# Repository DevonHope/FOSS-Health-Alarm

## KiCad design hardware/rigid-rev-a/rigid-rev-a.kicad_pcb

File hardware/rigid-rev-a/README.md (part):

# WakeBand rigid rev A (KiCad project)

4-layer 0.8 mm rigid board that replaces the flex design (archived in
`../flex-rev-a`). Routed, DRC clean, fab package in `fab/`. Last edited with
KiCad 10.0.3 (earlier revisions used 10.0.5; the file format is the same).

| Item | Value |
| --- | --- |
| Board | 33 x 15 mm, 1 mm corner radius, 0.8 mm FR4, ENIG |
| Pod | printed case rev A in `../case-rev-a` (one M2 screw); see below for the height stack |
| DRC | 0 violations, 0 unconnected, schematic parity 0 (1 documented exclusion); off-centre via ends checked as errors |
| Traces | straight or 45-degree segments only, 45-degree bends, every end on its pad or via centre (audit 2026-11-06, below) |
| ERC | 0 errors, 0 warnings |
| Vias | 140: 129 x 0.45/0.3 mm, 11 x 0.3/0.2 mm |
| Files | `rigid-rev-a-layout.pdf` (layers), `rigid-rev-a.pdf` (schematic), `fab/` |

## Stackup

JLCPCB JLC04081H-7628, 0.8 mm (also in `fab/gerbers/rigid-rev-a-job.gbrjob`):

| Layer | Use |
| --- | --- |
| F.Cu (L1, 35 um) | all SMT parts, two UART bench pads (J601 5-6, top edge), signal fan-out, GND pour |
| prepreg 7628, 0.21 mm | |
| In1.Cu (L2, 15 um) | solid GND, no tracks; no copper in the antenna keep-out |
| core 0.26 mm | |
| In2.Cu (L3, 15 um) | power jumps (VSYS, VBAT, VIN, VDD_2V0, LRA_P, nRESET) and signal routing; GND fill in the spare area |
| prepreg 7628, 0.21 mm | |
| B.Cu (L4, 35 um) | faces the cell and LRA: the four dock landing pads (J601 1-4), hand-solder pads TP201/TP202/TP501/TP502, JP201, signal routing, GND pour; no parts |

Track length by layer: F.Cu 208 mm, In2.Cu 205 mm, B.Cu 147 mm, In1.Cu 0.

## Orientation, outline and pod height

The board mounts **parts-side out** (changed 2026-11-06): F.Cu, with every
part, faces the case top, the pod's outer face. B.Cu has no parts and faces
the cell and the LRA, which sit between the board and the wrist.

**Dock contacts (changed 2026-11-07): four landing pads on B.** J601 pads
1-4 are Ø1.6 mm ENIG pads on B.Cu in a column at x 131.5, beside the LRA:
SWDCLK (y 101.1), SWDIO (103.3), GND (111.7), VIN (113.9). Four Mill-Max
0906-2 spring pins on the contact carrier in the wrist cover press on them
(see `../case-rev-a` and `../contact-carrier-rev-a`); nothing is soldered to
them. J601 pads 5-6 (UART_RX x 123.75, UART_TX x 121.75, y 101.6) stay on F
as bench test pads; the dock no longer carries UART (it uses SWD + RTT).
Coordinates below are KiCad board coordinates, with the board from
(100, 100) to (133, 115). The strip along the top edge (x 119.8-133) has
no parts, so the case top's land sits right on the board there and takes
the push of the top pair of spring pins.

Pod height, from the outer face (case rev A):

| Layer | mm |
| --- | --- |
| case top | 1.2 |
| tallest F part (L201, 0603 caps, SOD-123F) plus 0.2 mm | 1.3 |
| board | 0.8 |
| gap (B.Cu has no parts) | 0.2 |
| cell, up to | 5.0 |
| foam | 0.5 |
| wrist cover floor | 1.0 |
| **Total** | **about 10** (9 with a 4 mm cell) |

## Envelopes (Dwgs.User)

| Envelope | Where | Notes |
| --- | --- | --- |
| ISP2454 antenna keep-out | x 100-105, full height | rule area inside the U1 footprint: no tracks, vias or pours on any layer |
| 60 mAh cell, 17 x 13.5 mm | x 107-124, y 100.75-114.25 | under B; starts 2 mm past the keep-out; PCM and lead end at x = 124 |
| Ø8 LRA (Ø8.5 envelope) | centre (128.75, 107.5), x 124.5-133 | under B, far end of the board; circle top at y 103.25, bottom at 111.75 |

## 3D models

Every part on the board has a 3D model, except the test pads, the dock
pads, NT201 and JP201, which need none. KiCad 10 has no model for two
footprints, so `wakeband.3dshapes/` holds parametric ones (build123d; rebuild
with `pip install build123d`, then from this folder
`python wakeband.3dshapes/make_models.py wakeband.3dshapes`):

| Model | Used by | Size and source |
| --- | --- | --- |
| `InsightSiP_ISP2454_LGA-62_8x8mm.step` | U1 (also set in `wakeband.pretty`) | 8 x 8 x 1.0 mm, substrate plus overmould, pin-1 dot; size from the footprint |
| `Texas_DPY0002A_0.6x1mm_P0.65mm.step` | D602-D605 | 1.0 x 0.6 x 0.375 mm X1SON-2, bottom terminals, pin-1 band; TI MPSS034C |
| `LiPo_3.7V_60mAh_401215_PCM.step` | cell (off board) | 17 x 13 x 4.0 mm pouch with folded PCM at +X, lead stubs |
| `Vybronics_VG0832012_LRA_D8x3.25mm.step` | LRA (off board) | Ø8.0 x 3.25 mm can, lead tab at +X |
| `LED_TOGIALED_1615_RGB_CommonAnode.step` | D702 | 1.6 x 1.5 x 0.6 mm body and lens, pin-1 (anode) mark |
| `Kinetic_UTDFN-8_1.5x1.5mm_P0.4mm_EP1.45x0.8mm.step` | U202 | 1.5 x 1.5 x 0.5 mm UTDFN-8, pin-1 dot, terminals |

The paths use `${KIPRJMOD}`. D602-D605 use the KiCad library footprint
`Package_SON:Texas_DPY0002A_0.6x1mm_P0.65mm`; "Update footprint from library"
puts back the library's model path, which has no file in KiCad 10.

`make_placed.py` places the cell and the LRA in the board's STEP frame,
under B.Cu with a 0.2 mm gap: the cell centred at (115.5, 107.5) with its
lead end at x = 124, and the LRA centred at (128.75, 107.5) with its lead tab
turned towards TP501. The leads run to TP201 (bottom right) and TP202 (top
right) and to TP501/TP502. A clash check against the board's STEP finds no
overlaps. The tallest F part is now 1.1 mm (SW201 was removed on
2026-11-07); the charge LED is 0.6 mm.

## Placement

- **U1 ISP2454** at the left end, antenna end in the keep-out strip.
- **U401 LIS2DW12** just right of the module's top corner. C401 and C402
  sit right of it, 1.0 mm of track from pins 9 and 10; their GND pads share
  one via, and U401's GND pads 5-8 share another.
- **U201 nPM1304** in the middle. The BUCK1 parts sit left of it (see
  "Buck loop" below).
- **Charger caps** stacked right of U201, each beside its pin: C206
  (VBUSOUT, pin 22), C201 (VIN, pin 21), C205 (VSYS, pin 20), C202 (VBAT,
  pin 19). Their GND pads are joined by an F.Cu spine with three vias to
  In1 between the pads. R202 (VSET1) and R201 (DNP) sit below the stack.
  C203 sits under PMIC pin 12, offset left so pins 13-15 can escape.
- **JP201** (I_BAT jumper) on B in the bottom-right corner, between the
  cell's lead end and TP201, outside the cell and LRA outlines, so it can
  be cut for current measurement with the cell fitted.
- **Dock landing pads** J601 on B at x 131.5 (see Orientation). Their
  protection parts stay along the bottom edge: R601-R604 and D602-D605 (TI
  DPY package) between the module and D601 (VIN TVS).
- **U501 DRV2605L** at the right end over the LRA envelope, with C501, C502.
- **Hand-solder pads** on B (the cell side), 0.5 mm to other copper and
  mask at pad + 0.1 mm, all outside the cell and LRA outlines: TP201 (BAT+)
  at (129.0, 113.5) and JP201 in the bottom-right corner below the LRA
  circle; along the top edge TP502 (LRA-) at (125.5, 101.5), TP501 (LRA+)
  at (127.0, 101.5) and TP202 (BAT-, 1.5 mm pad) at (129.05, 101.6), all
  left of the dock landing pads. TP202 joins the B GND pour; TP501 has a
  filled via in its pad. TH201 sits on F over the cell, through the board.
- **Charge LED** D702 (RGB, 1.6 x 1.5 mm) at (130.225, 113.2), in SW201's old
  place at the bottom edge below U501, with its driver U202 (KTD2026) at
  (126.55, 113.2) and C208 (1 uF, VIN) at (128.1, 112.17). See "Charge LED"
  below.
- **Test pads**: TP702 (I2C_SDA) and TP704 (VDD_2V0) at the top edge near
  TH201, TP703 (I2C_SCL) left of U501, TP706 (VBAT) beside R201, TP401
  (ACC_INT2), TP701 (nRESET), TP705 (VSYS), TP707 (GND) and TP203
  (SHPHLD; with SW201 gone, this pad is the only way to pull SHPHLD low).
  TP704 has a filled via in its pad (flat after POFV, still
  probeable).

## Buck loop (nPM1304 BUCK1, pins 1-4)

Laid out after Nordic's reference: input cap across PVDD/PVSS1 at the pins,
output cap between the inductor and PVSS1, PVSS1 tied to GND only at the net
tie next to pin 2.

| Path (pad centre to pad centre, along the copper) | Now | Before the review |
| --- | --- | --- |
| C204.2 (PVSS1) to pin 2 | 1.7 mm, no vias | 5.4 mm |
| C204.1 (VSYS) to pin 4 (PVDD) | 1.7 mm, no vias | 3.3 mm, 2 vias |
| C207.2 (PVSS1) to pin 2 | 4.2 mm, no vias | 7.3 mm, 2 vias |
| C207.1 to L201.2 | 2.3 mm (pad centres are 2.2 mm apart) | 2.9 mm |
| NT201.1 to pin 2 | 3.0 mm | 9.6 mm |
| L201.1 to pin 3 (SW1) | 2.9 mm | 1.1 mm |
| C205.1 (VSYS) to pin 20 | 1.5 mm | 13.0 mm |
| pin 4 to pin 20 (VSYS) | 12.4 mm, 2 vias | 23.9 mm, 4 vias |

"Now" was measured after the 2026-11-06 trace clean-up, when every track
end sits on its pad centre; the clean-up moved these paths by 0.2 mm or
less.

- C204 sits 0.7 mm from pins 2 and 4. SW1 (0.3 mm) leaves pin 3 between
  C204's pads, under its body, to L201. The edge-to-edge copper of SW1 is
  2.2 mm: longer than before, the price of putting C204 across pins 2 and 4.
- C207 sits above L201; PVSS1 runs 0.4 mm wide from C207.2 through NT201.1
  and C204.2 to pin 2.
- NT201 sits on that PVSS1 link, 1.7 mm from pin 2, with its own GND via to
  In1 0.7 mm from its GND pad.
- Pin 1 (VOUT1, sense) drops through a via to In2 and lands at the
  L201.2/C207.1 node.
- Pin 4 and C204.1 change layer through two VSYS vias to two 0.2 mm In2
  tracks under the PMIC exposed pad (one in each gap between the EP via
  rows), which end in a via in C205.1's pad next to pin 20. Pin 32 joins
  through its own via. VSYS to U501/C501 runs on F from pin 32 along the
  top of the PMIC area.

## Routing

- Power: 0.4 mm on the battery path (BATT_P 0.5 mm, VBAT), 0.3 mm on
  VIN/VSYS/SW1/LRA, 0.4 mm on PVSS1 between the caps, 0.25 mm at the PMIC
  pins, 0.2 mm VSYS under the EP, 0.25 mm on VDD_2V0 where it leaves the
  buck. VBAT changes layer with two vias at each end. Single vias remain on
  VSYS (pin 32 and the via in C205.1), VIN (the via in C201.1, at
  (123.1, 111.75) and at the dock, (122.65, 113.2)), VDD_2V0 and LRA_P at
  U501 (129.15, 106.4). Each via is good for about 1 A, well above these
  currents.
- Signals: 0.12 mm tracks, 0.10 mm clearance, VDD_2V0 and REG 0.2 mm,
  routed with a scripted grid router because Freerouting crashed on this
  board, then cleaned up (see "Trace audit" below). The router keeps vias
  out of pads. I2C runs U401 - U1 - U201 - U501
  with test pads TP702/TP703.
- Dock lines (rework 2026-11-06): the pads moved from B (bottom edge) to F
  (top edge), and each line now runs from its pad across the board to its
  TVS and 100 ohm resistor at the bottom edge, then on to the module:
  UART_TX 28.8 mm / 3 vias, UART_RX 27.0 / 3, SWDIO 41.9 / 4 (round the
  module end), SWDCLK 27.3 / 2, VIN 23.8 mm / 3 vias to C201.1. These were
  laid by a small 3-layer grid router (F, In2, B; In1 stays solid GND) and
  then checked by DRC and the trace audit; three spots were laid by hand.
- Rules (in `rigid-rev-a.kicad_dru` and the netclasses): 0.10 mm clearance
  on all netclasses, 0.2 mm hole clearance, 0.2 mm from vias to other copper
  on inner layers, 0.5 mm around the hand-solder pads. Zones use 0.2 mm
  clearance.
- ANT_LINK (module pads 20 and 22) is joined on F.Cu, 0.65 mm long, right at
  the keep-out edge over the solid In1 GND.
- No F.Cu tracks inside the module's or the PMIC's pad ring (nRESET and
  some signals pass under the module on In2/B, outside the keep-out).
  VDD_2V0 passes under U401 between its pads, and REG and I2C pass under
  the U501 body; all are under solder mask.

## GND, stitching and vias

- In1 is solid GND. F, B and the spare area of In2 are GND pours (0.2 mm
  clearance, islands removed).
- Each F-side GND pad has its own via to In1 where there is room, plus
  stitching vias around the board edge and at the module's top and bottom
  (outside the keep-out).
- Shared GND vias: U401 pads 5-8 share one; C401 and C402 share one; the
  four charger caps share three on their GND spine. TP202 (BAT-) on B
  joins the B GND pour; the GND landing pad has a via at its edge.
- Each data TVS (D602-D605) has its own GND via about 0.8 mm from its GND
  pad.
- Two 0.3/0.2 mm GND vias under the U501 body tie the pin 4 and pin 8 pour
  pockets to In1.

| Vias | Count |
| --- | --- |
| 0.45/0.3, signal and power | 76 |
| 0.45/0.3, GND (incl. 9 in the nPM1304 exposed pad, 4 in module corner pads, 1 in dock pad 2) | 49 |
| 0.3/0.2, GND (8 in module pads, 2 under U501) | 10 |
| 0.3/0.2, nRESET (module pad 13) | 1 |
| Total | 136 |

### Vias in pads and POFV

The ISP2454 pads that sit inside the outer ring cannot be reached by a
track on F.Cu. Their outcome:

- **Interior GND pads** 8, 12, 14, 16, 18, 24 (column x = 105.2) and 21, 23
  (column x = 105.85) each have a 0.3/0.2 mm via in the pad. The large GND
  pads 1, 7, 25, 31 have 0.45/0.3 mm vias in the pad.
- **nRESET (pad 13)** has a 0.3/0.2 via in the pad and runs on In2 to TP701.
- **Pad 10** stays NC. The other inner pads are unused nets, left
  unconnected.

Other vias in pads: nine in the nPM1304 exposed pad, TP701 (nRESET), C201.1
(VIN), C205.1 (VSYS), TP704 (VDD_2V0), TP501 (LRA+), D601.1 (VIN), the
SWDCLK landing pad (J601.3, centre) and the edges of the VIN and GND landing
pads (J601.1, J601.2). All of these need JLCPCB's
**epoxy-filled and capped (POFV)** option, which fills every via on the
board.

## DRC and ERC

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
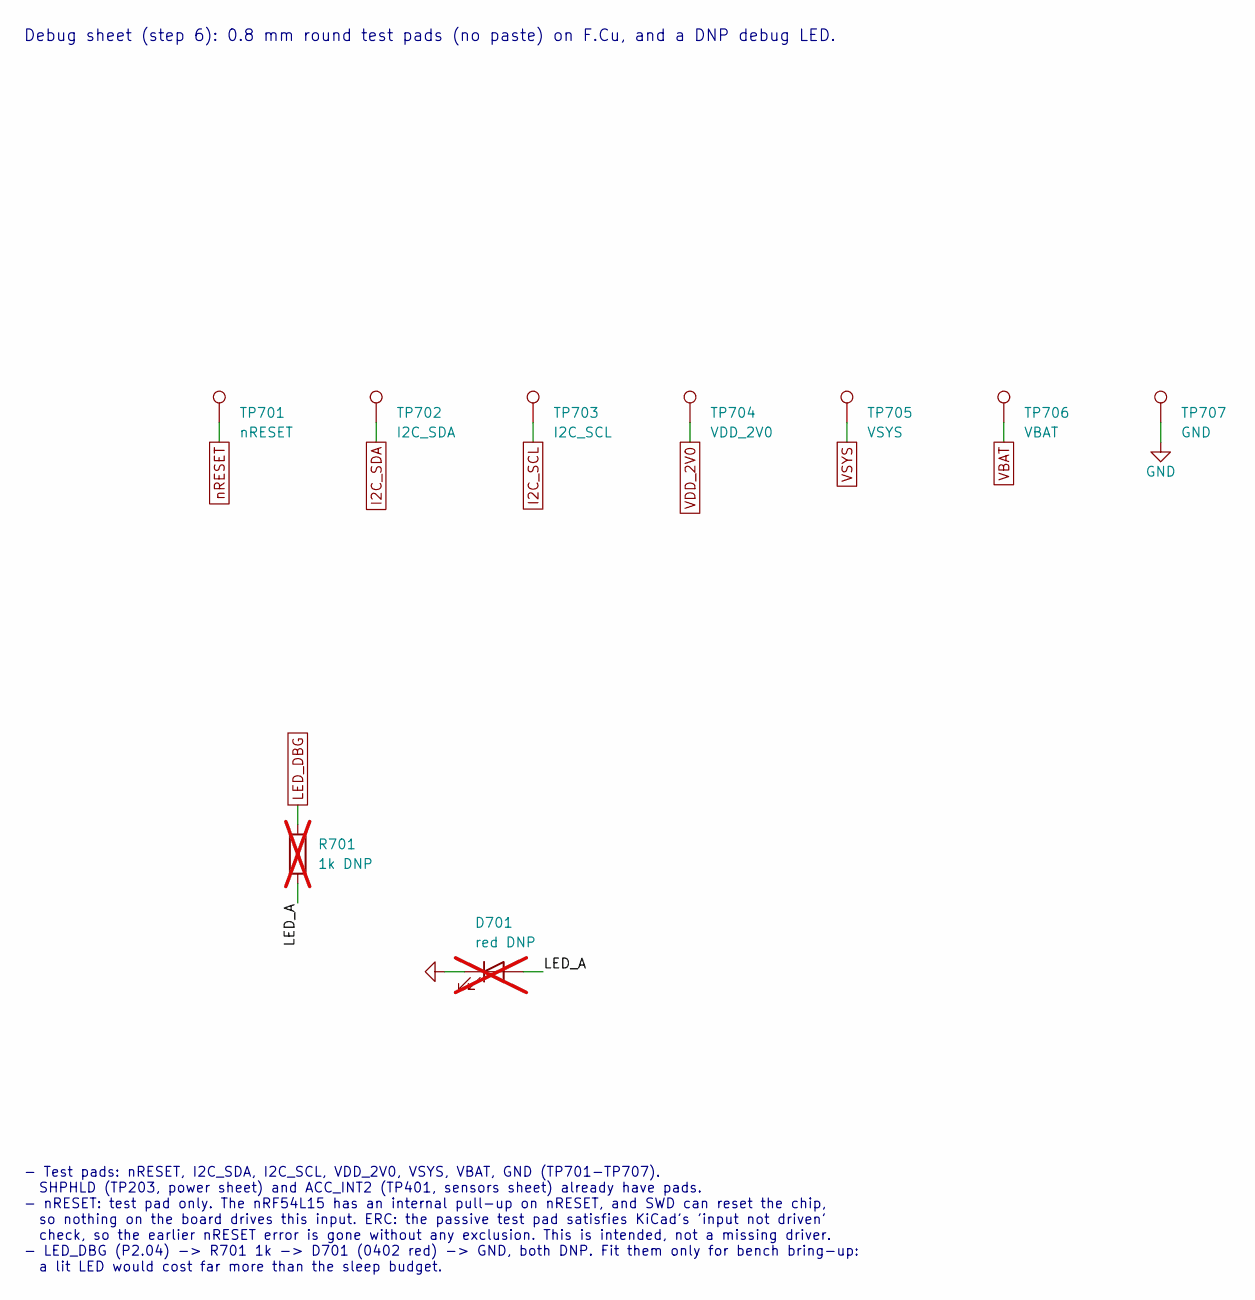
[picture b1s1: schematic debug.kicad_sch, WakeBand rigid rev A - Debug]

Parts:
D701: red DNP; LED_0402_1005Metric; MPN XINGLIGHT XL-1005SURC; LCSC C25503345; not fitted
R701: 1k DNP; R_0402_1005Metric; LCSC C11702; not fitted
TP701: nRESET; TestPoint_Pad_D0.8mm
TP702: I2C_SDA; TestPoint_Pad_D0.8mm
TP703: I2C_SCL; TestPoint_Pad_D0.8mm
TP704: VDD_2V0; TestPoint_Pad_D0.8mm
TP705: VSYS; TestPoint_Pad_D0.8mm
TP706: VBAT; TestPoint_Pad_D0.8mm
TP707: GND; TestPoint_Pad_D0.8mm

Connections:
/debug/LED_A: D701.2 (A), R701.2
GND: D701.1 (K), TP707.1; also elsewhere on the board
I2C_SCL: TP703.1; also elsewhere on the board
I2C_SDA: TP702.1; also elsewhere on the board
LED_DBG: R701.1; also elsewhere on the board
VBAT: TP706.1; also elsewhere on the board
VDD_2V0: TP704.1; also elsewhere on the board
VSYS: TP705.1; also elsewhere on the board
nRESET: TP701.1; also elsewhere on the board

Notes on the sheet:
- Test pads: nRESET, I2C_SDA, I2C_SCL, VDD_2V0, VSYS, VBAT, GND (TP701-TP707). SHPHLD (TP203, power sheet) and ACC_INT2 (TP401, sensors sheet) already have pads. - nRESET: test pad only. The nRF54L15 has an internal pull-up on nRESET, and SWD can reset the chip, so nothing on the board drives this 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
Debug sheet (step 6): 0.8 mm round test pads (no paste) on F.Cu, and a DNP debug LED.

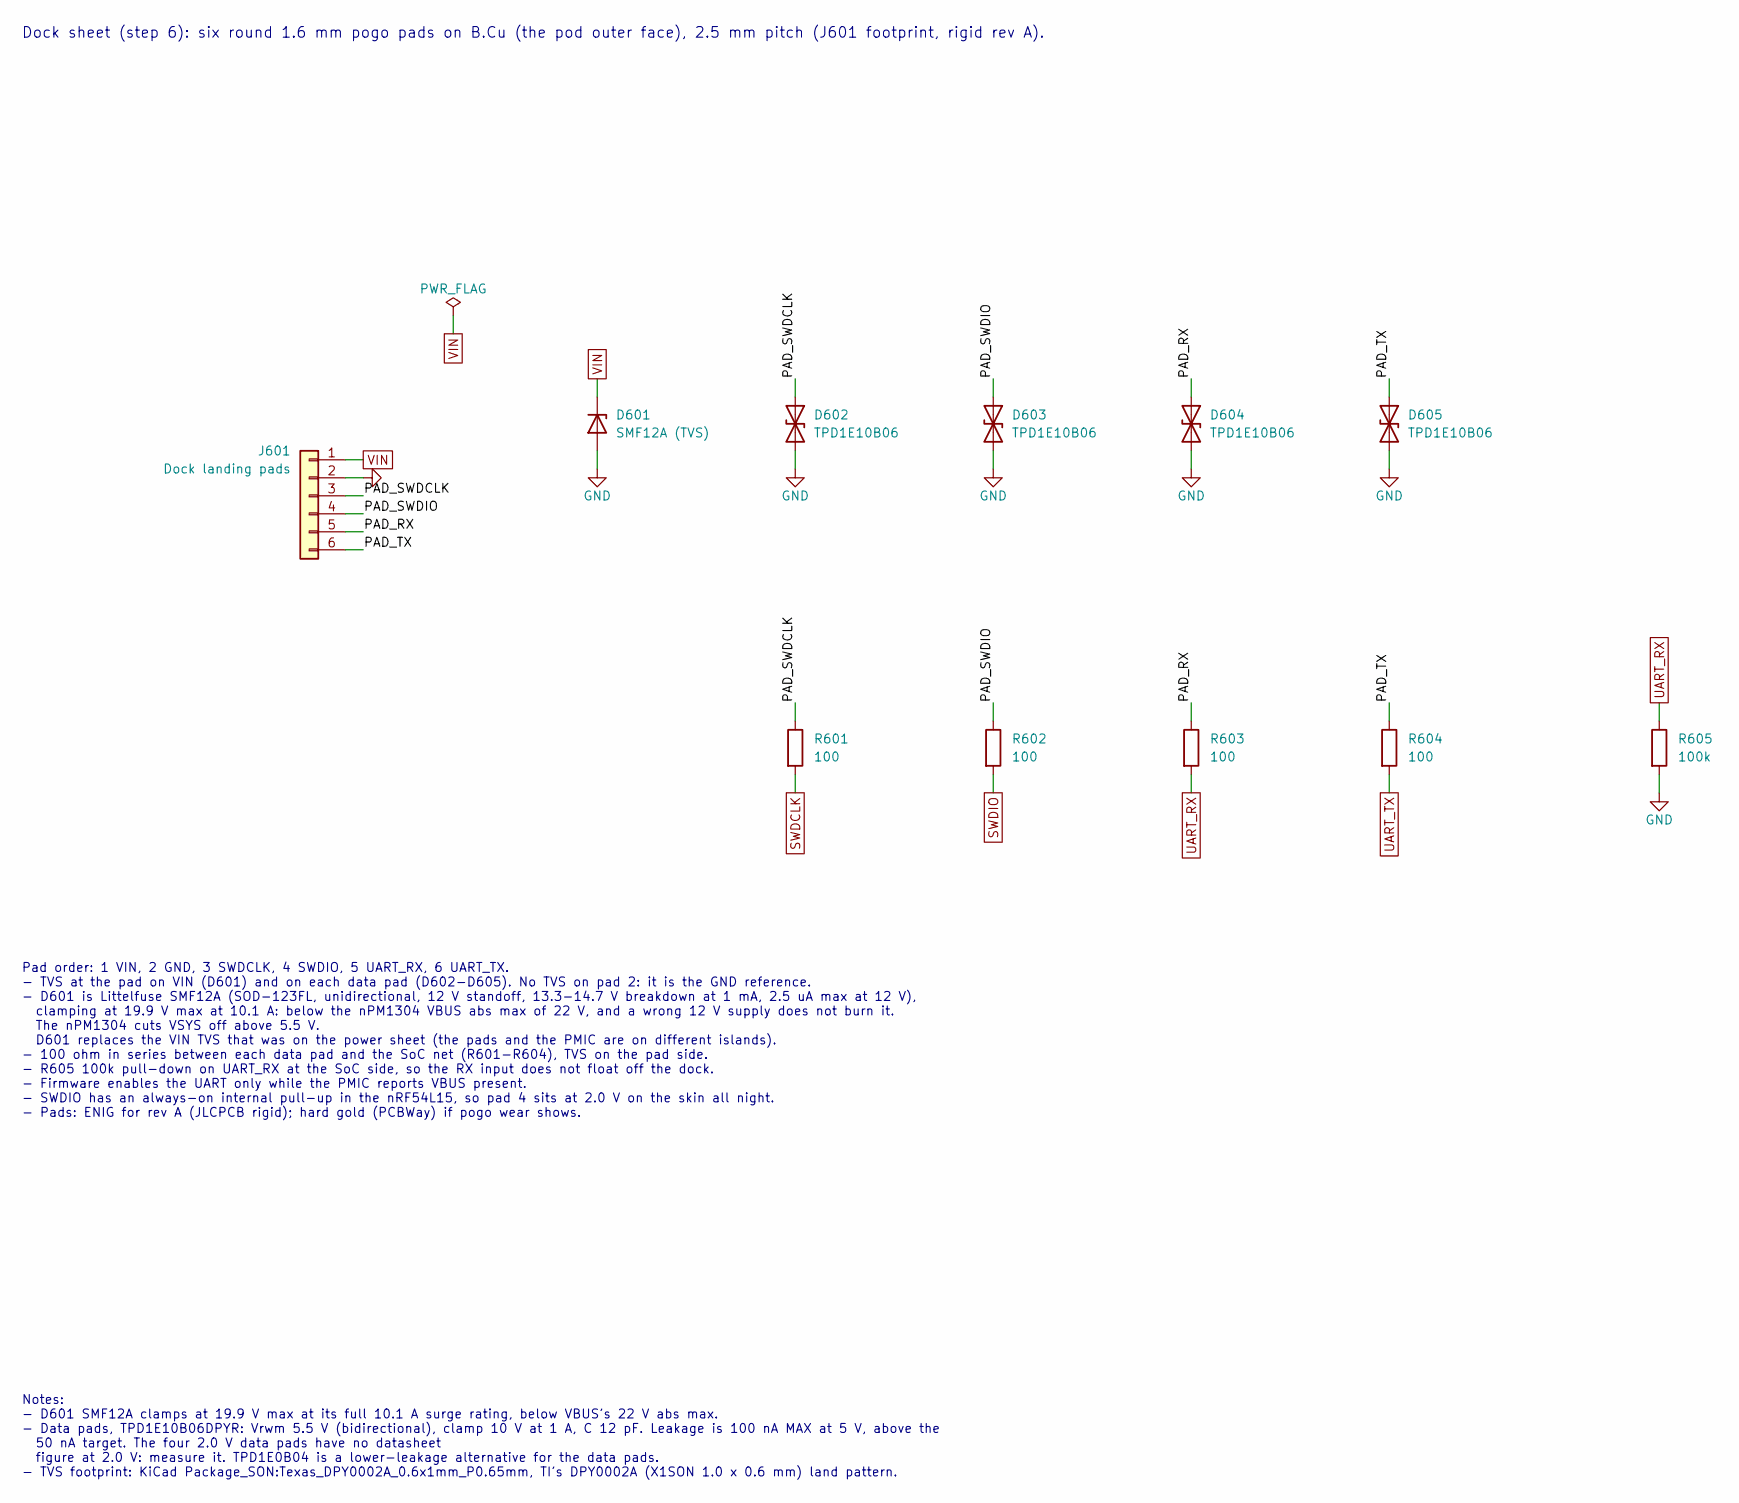
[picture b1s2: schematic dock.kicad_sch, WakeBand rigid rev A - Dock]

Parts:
D601: SMF12A (TVS); D_SOD-123F; MPN Littelfuse SMF12A; LCSC C207255
D602, D603, D604, D605: TPD1E10B06; Texas_DPY0002A_0.6x1mm_P0.65mm; MPN TI TPD1E10B06DPYR; LCSC C48260
J601: Dock landing pads; DockLanding_4xB_D1.6mm_2xUART
R601, R602, R603, R604: 100; R_0402_1005Metric; LCSC C25076
R605: 100k; R_0402_1005Metric; LCSC C25741

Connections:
/dock/PAD_RX: D604.1 (A1), J601.5, R603.1
/dock/PAD_SWDCLK: D602.1 (A1), J601.3, R601.1
/dock/PAD_SWDIO: D603.1 (A1), J601.4, R602.1
/dock/PAD_TX: D605.1 (A1), J601.6, R604.1
GND: D601.2 (A), D602.2 (A2), D603.2 (A2), D604.2 (A2), D605.2 (A2), J601.2, R605.2; also elsewhere on the board
SWDCLK: R601.2; also elsewhere on the board
SWDIO: R602.2; also elsewhere on the board
UART_RX: R603.2, R605.1; also elsewhere on the board
UART_TX: R604.2; also elsewhere on the board
VIN: D601.1 (K), J601.1; also elsewhere on the board

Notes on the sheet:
Pad order: 1 VIN, 2 GND, 3 SWDCLK, 4 SWDIO, 5 UART_RX, 6 UART_TX. - TVS at the pad on VIN (D601) and on each data pad (D602-D605). No TVS on pad 2: it is the GND reference. - D601 is Littelfuse SMF12A (SOD-123FL, unidirectional, 12 V standoff, 13.3-14.7 V breakdown at 1 mA, 2.5 uA max at 12 V), cla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
Dock sheet (step 6): six round 1.6 mm pogo pads on B.Cu (the pod outer face), 2.5 mm pitch (J601 footprint, rigid rev A).
Notes: - D601 SMF12A clamps at 19.9 V max at its full 10.1 A surge rating, below VBUS's 22 V abs max. - Data pads, TPD1E10B06DPYR: Vrwm 5.5 V (bidirectional), clamp 10 V at 1 A, C 12 pF. Leakage is 100 nA MAX at 5 V, above the 50 nA target. The four 2.0 V data pads have no datasheet figure at 2.0 V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

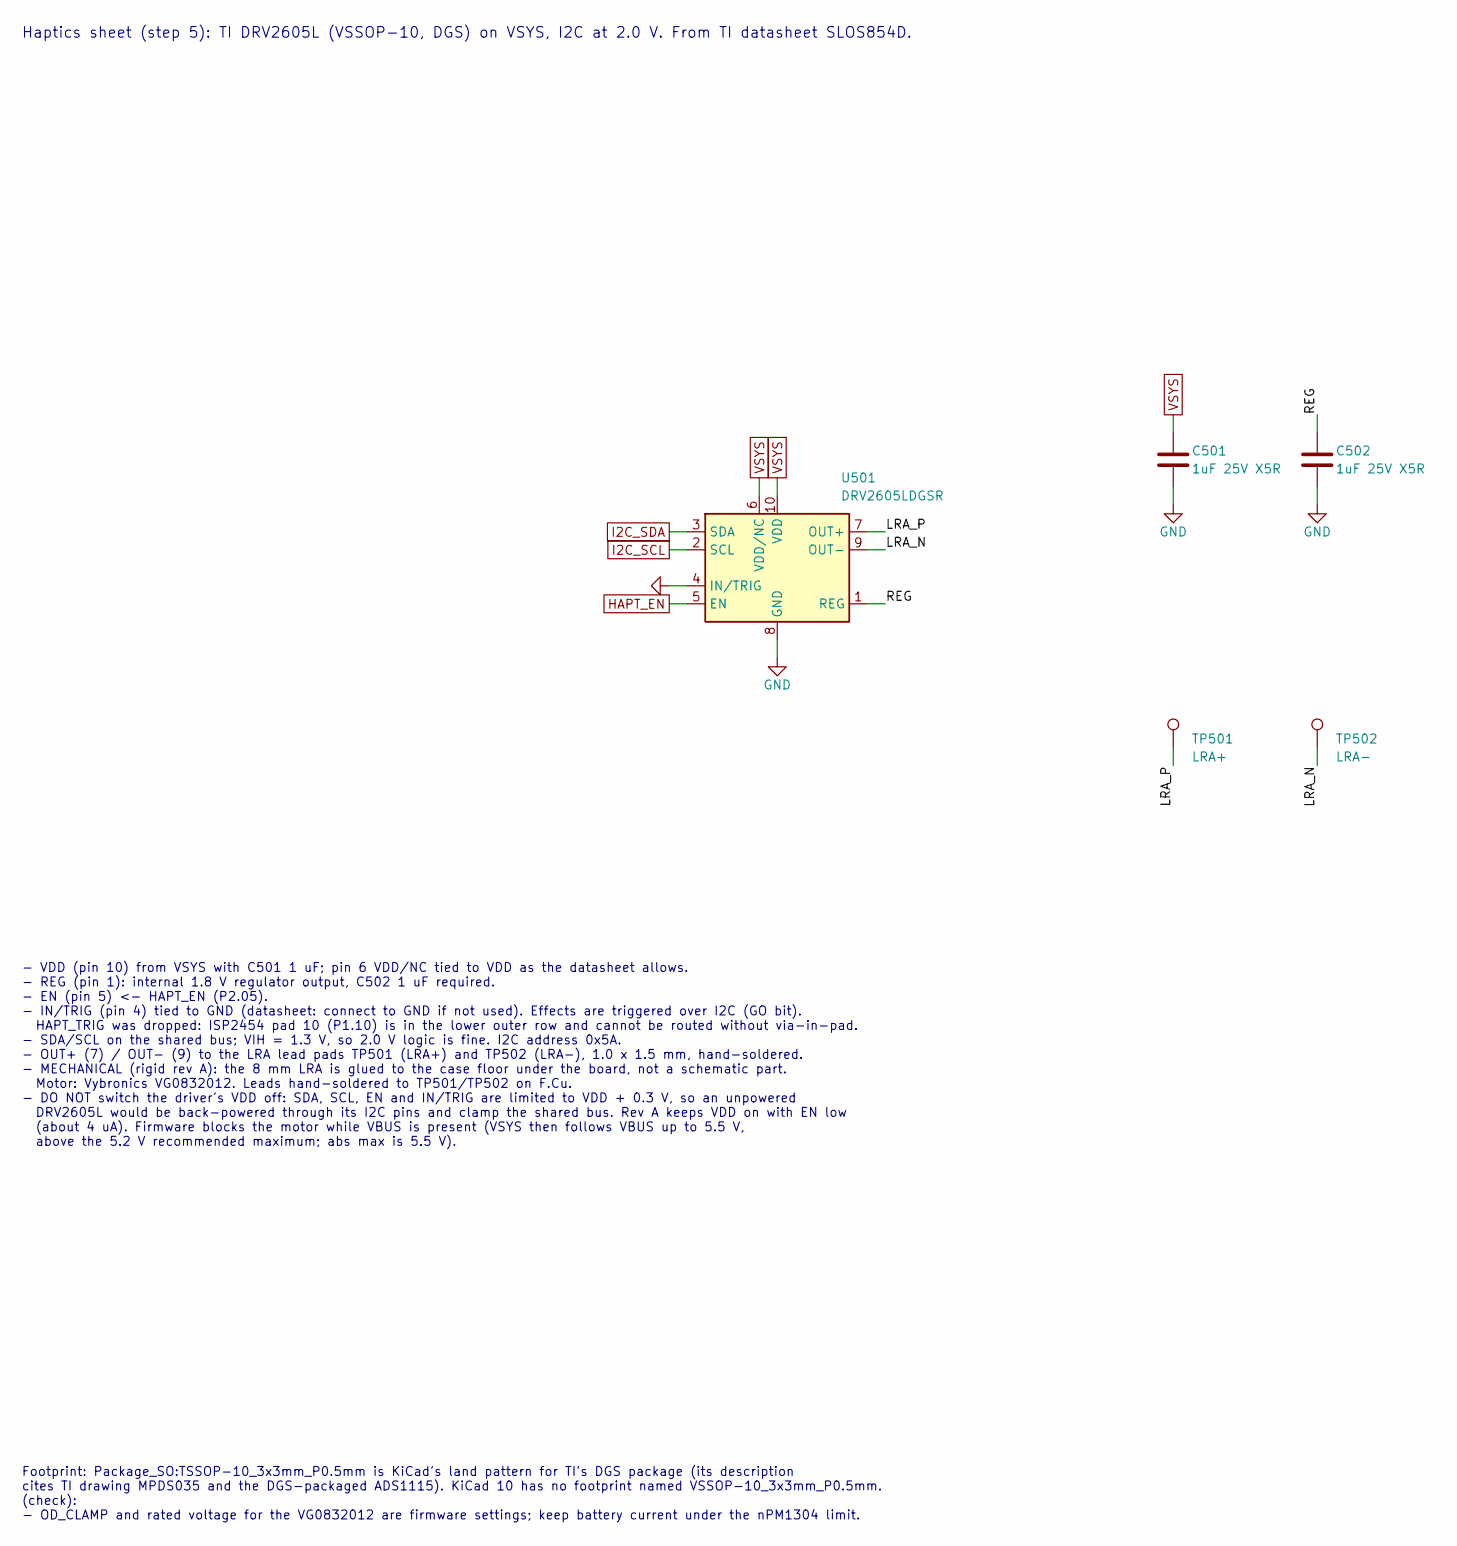
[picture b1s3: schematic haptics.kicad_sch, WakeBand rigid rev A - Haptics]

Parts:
C501, C502: 1uF 25V X5R; C_0402_1005Metric; LCSC C52923
TP501: LRA+; Pad_SMD_1.0x1.5mm
TP502: LRA-; Pad_SMD_1.0x1.5mm
U501: DRV2605LDGSR; TSSOP-10_3x3mm_P0.5mm; LCSC C527464

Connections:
/haptics/LRA_N: TP502.1, U501.9 (OUT-)
/haptics/LRA_P: TP501.1, U501.7 (OUT+)
/haptics/REG: C502.1, U501.1 (REG)
GND: C501.2, C502.2, U501.4 (IN/TRIG), U501.8 (GND); also elsewhere on the board
HAPT_EN: U501.5 (EN); also elsewhere on the board
I2C_SCL: U501.2 (SCL); also elsewhere on the board
I2C_SDA: U501.3 (SDA); also elsewhere on the board
VSYS: C501.1, U501.6 (VDD/NC), U501.10 (VDD); also elsewhere on the board

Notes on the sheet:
Footprint: Package_SO:TSSOP-10_3x3mm_P0.5mm is KiCad's land pattern for TI's DGS package (its description cites TI drawing MPDS035 and the DGS-packaged ADS1115). KiCad 10 has no footprint named VSSOP-10_3x3mm_P0.5mm. (check): - OD_CLAMP and rated voltage for the VG0832012 are firmware settings; kee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
Haptics sheet (step 5): TI DRV2605L (VSSOP-10, DGS) on VSYS, I2C at 2.0 V. From TI datasheet SLOS854D.
- VDD (pin 10) from VSYS with C501 1 uF; pin 6 VDD/NC tied to VDD as the datasheet allows. - REG (pin 1): internal 1.8 V regulator output, C502 1 uF required. - EN (pin 5) <- HAPT_EN (P2.05). - IN/TRIG (pin 4) tied to GND (datasheet: connect to GND if not used). Effects are triggered over I2C (GO b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

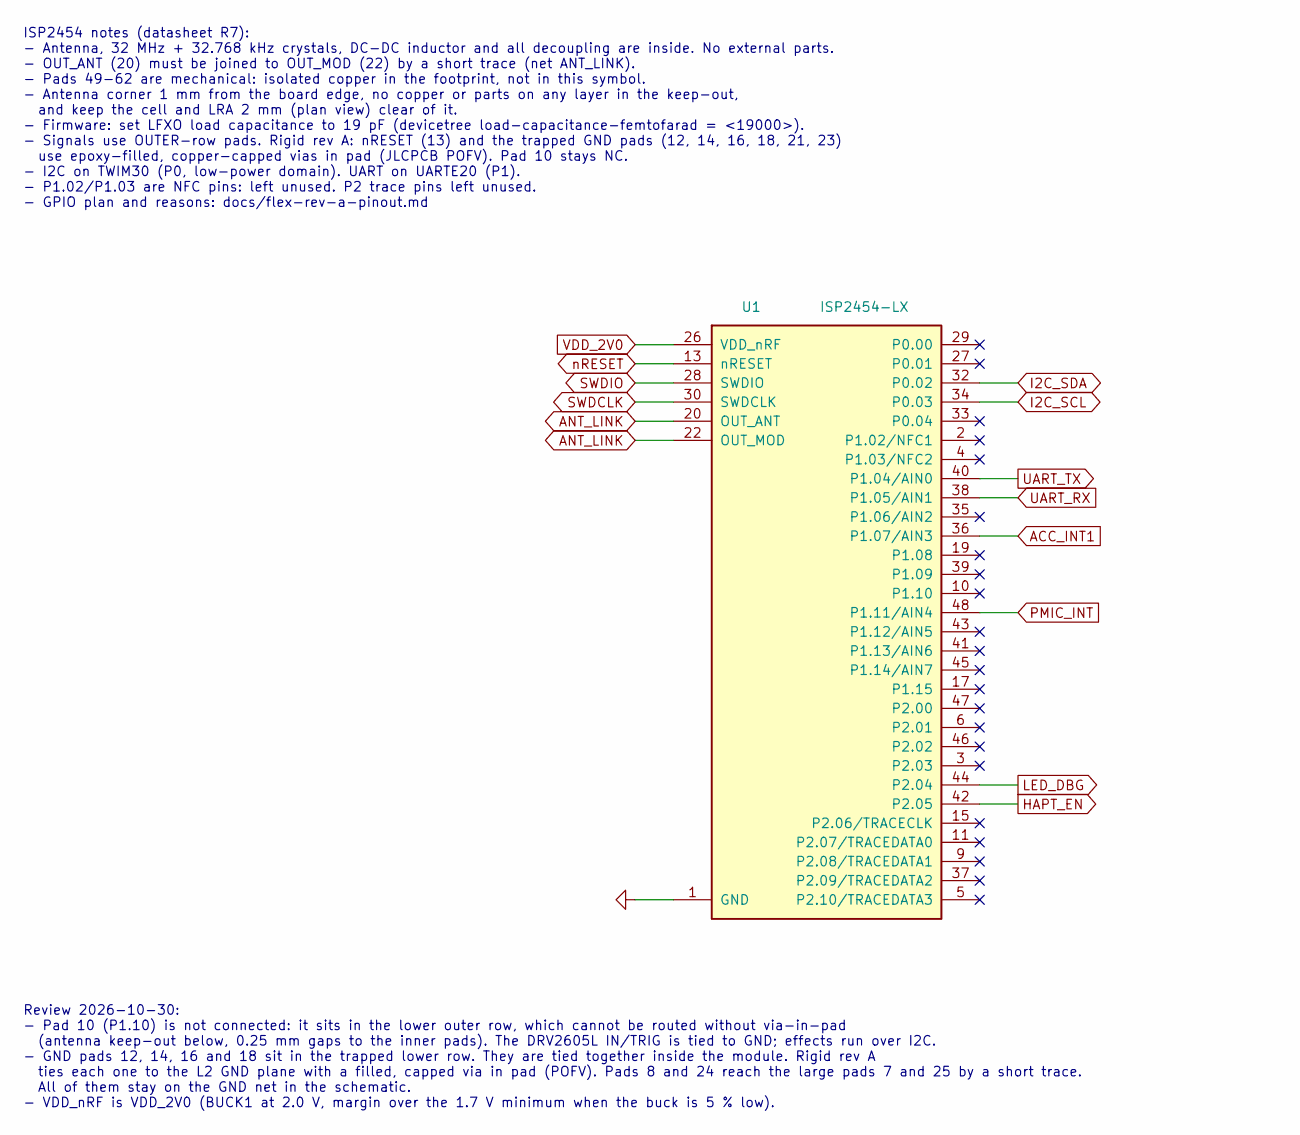
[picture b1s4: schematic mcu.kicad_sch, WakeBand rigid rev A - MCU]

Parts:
U1: ISP2454-LX; InsightSiP_ISP2454_LGA-62_8x8mm

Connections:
ACC_INT1: U1.36 (P1.07/AIN3); also elsewhere on the board
ANT_LINK: U1.20 (OUT_ANT), U1.22 (OUT_MOD)
GND: U1.1 (GND), U1.7 (GND), U1.8 (GND), U1.12 (GND), U1.14 (GND), U1.16 (GND), U1.18 (GND), U1.21 (GND), U1.23 (GND), U1.24 (GND), U1.25 (GND), U1.31 (GND); also elsewhere on the board
HAPT_EN: U1.42 (P2.05); also elsewhere on the board
I2C_SCL: U1.34 (P0.03); also elsewhere on the board
I2C_SDA: U1.32 (P0.02); also elsewhere on the board
LED_DBG: U1.44 (P2.04); also elsewhere on the board
PMIC_INT: U1.48 (P1.11/AIN4); also elsewhere on the board
SWDCLK: U1.30 (SWDCLK); also elsewhere on the board
SWDIO: U1.28 (SWDIO); also elsewhere on the board
UART_RX: U1.38 (P1.05/AIN1); also elsewhere on the board
UART_TX: U1.40 (P1.04/AIN0); also elsewhere on the board
VDD_2V0: U1.26 (VDD_nRF); also elsewhere on the board
nRESET: U1.13 (nRESET); also elsewhere on the board

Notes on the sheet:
Review 2026-10-30: - Pad 10 (P1.10) is not connected: it sits in the lower outer row, which cannot be routed without via-in-pad (antenna keep-out below, 0.25 mm gaps to the inner pads). The DRV2605L IN/TRIG is tied to GND; effects run over I2C. - GND pads 12, 14, 16 and 18 sit in the trapped lower 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
ISP2454 notes (datasheet R7): - Antenna, 32 MHz + 32.768 kHz crystals, DC-DC inductor and all decoupling are inside. No external parts. - OUT_ANT (20) must be joined to OUT_MOD (22) by a short trace (net ANT_LINK). - Pads 49-62 are mechanical: isolated copper in the footprint, not in this symbol. -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

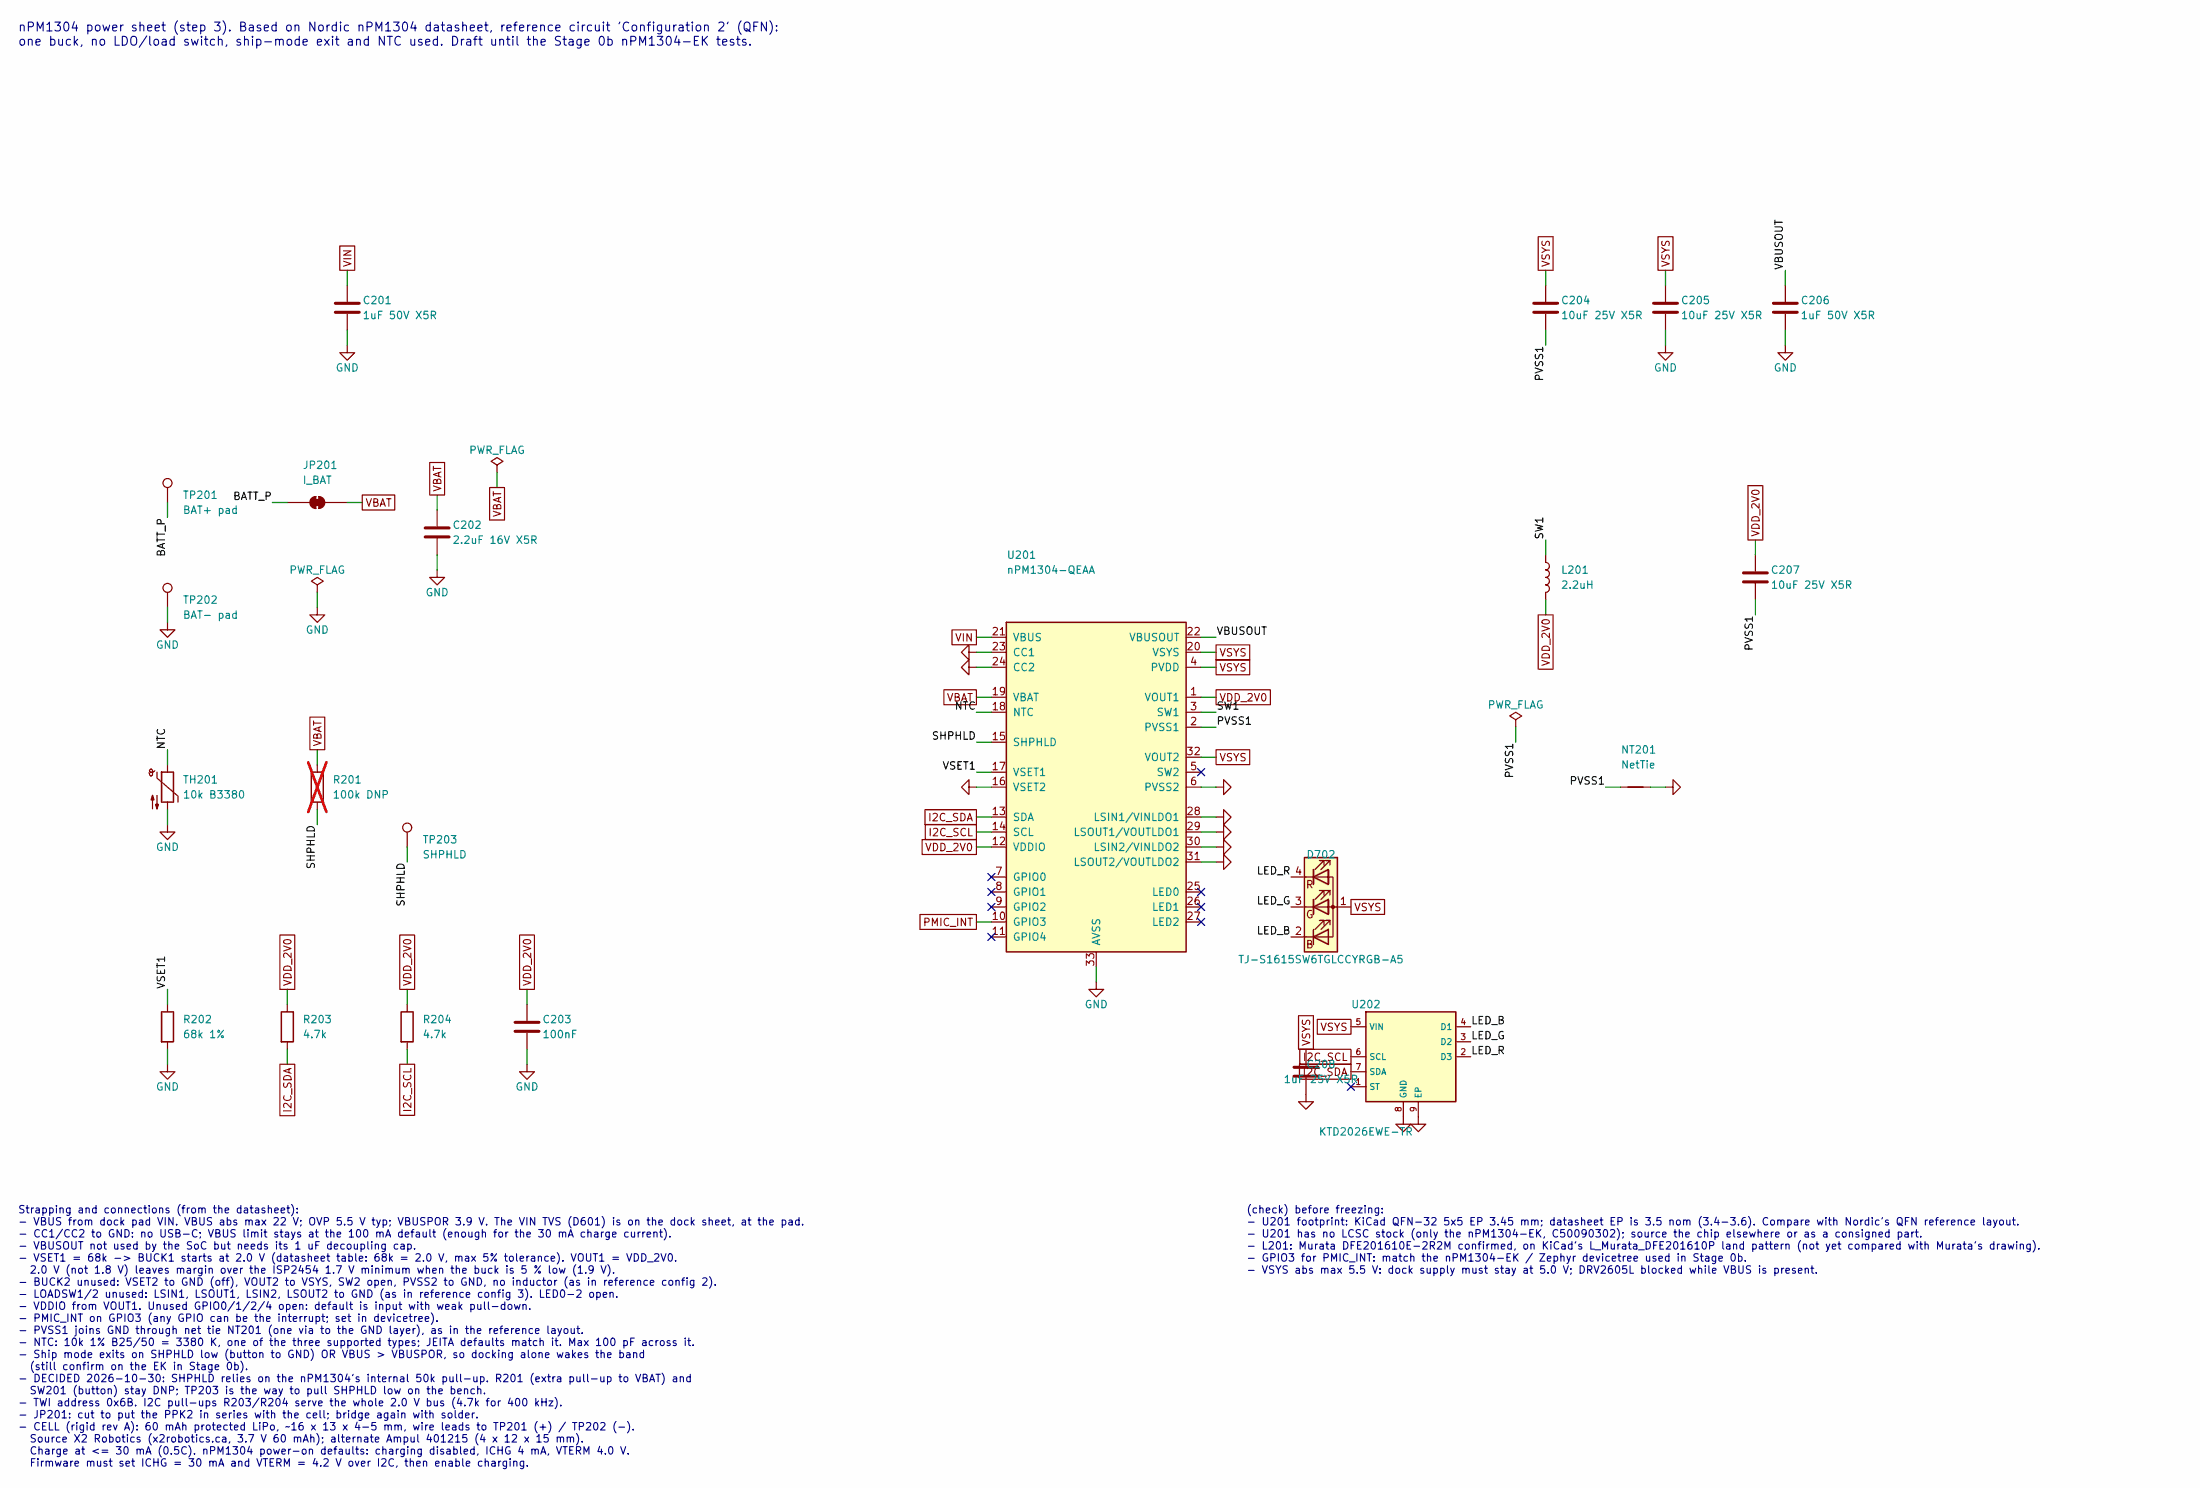
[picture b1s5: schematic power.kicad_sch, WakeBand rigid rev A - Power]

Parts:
C201, C206: 1uF 50V X5R; C_0603_1608Metric; LCSC C15849
C202: 2.2uF 16V X5R; C_0603_1608Metric; LCSC C23630
C203: 100nF; C_0402_1005Metric; LCSC C1525
C204, C205, C207: 10uF 25V X5R; C_0603_1608Metric; LCSC C96446
C208: 1uF 25V X5R; C_0402_1005Metric; LCSC C52923
D702: TJ-S1615SW6TGLCCYRGB-A5; LED_TOGIALED_1615_RGB_CommonAnode; LCSC C273610
JP201: I_BAT; SolderJumper-2_P1.3mm_Bridged_RoundedPad1.0x1.5mm
L201: 2.2uH; L_Murata_DFE201610P; MPN Murata DFE201610E-2R2M; LCSC C337891
NT201: NetTie; NetTie-2_SMD_Pad0.5mm
R201: 100k DNP; R_0402_1005Metric; LCSC C25741; not fitted
R202: 68k 1%; R_0402_1005Metric; LCSC C36871
R203, R204: 4.7k; R_0402_1005Metric; LCSC C25900
TH201: 10k B3380; R_0402_1005Metric; MPN Murata NCP15XH103F03RC; LCSC C77131
TP201: BAT+ pad; TestPoint_Pad_2.0x2.0mm
TP202: BAT- pad; TestPoint_Pad_1.5x1.5mm
TP203: SHPHLD; TestPoint_Pad_1.0x1.0mm
U201: nPM1304-QEAA; QFN-32-1EP_5x5mm_P0.5mm_EP3.45x3.45mm
U202: KTD2026EWE-TR; Kinetic_UTDFN-8_1.5x1.5mm_P0.4mm_EP1.45x0.8mm; MPN Kinetic KTD2026EWE-TR

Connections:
/power/BATT_P: JP201.1 (A), TP201.1
/power/LED_B: D702.2 (BK), U202.4 (D1)
/power/LED_G: D702.3 (GK), U202.3 (D2)
/power/LED_R: D702.4 (RK), U202.2 (D3)
/power/NTC: TH201.1, U201.18 (NTC)
/power/PVSS1: C204.2, C207.2, NT201.1, U201.2 (PVSS1)
/power/SHPHLD: R201.2, TP203.1, U201.15 (SHPHLD)
/power/SW1: L201.1, U201.3 (SW1)
/power/VBUSOUT: C206.1, U201.22 (VBUSOUT)
/power/VSET1: R202.1, U201.17 (VSET1)
GND: C201.2, C202.2, C203.2, C205.2, C206.2, C208.2, NT201.2, R202.2, TH201.2, TP202.1, U201.6 (PVSS2), U201.16 (VSET2), U201.23 (CC1), U201.24 (CC2), U201.28 (LSIN1/VINLDO1), U201.29 (LSOUT1/VOUTLDO1), U201.30 (LSIN2/VINLDO2), U201.31 (LSOUT2/VOUTLDO2), U201.33 (AVSS), U202.8 (GND), U202.9 (EP); also elsewhere on the board
I2C_SCL: R204.2, U201.14 (SCL), U202.6 (SCL); also elsewhere on the board
I2C_SDA: R203.2, U201.13 (SDA), U202.7 (SDA); also elsewhere on the board
PMIC_INT: U201.10 (GPIO3); also elsewhere on the board
VBAT: C202.1, JP201.2 (B), R201.1, U201.19 (VBAT); also elsewhere on the board
VDD_2V0: C203.1, C207.1, L201.2, R203.1, R204.1, U201.1 (VOUT1), U201.12 (VDDIO); also elsewhere on the board
VIN: C201.1, U201.21 (VBUS); also elsewhere on the board
VSYS: C204.1, C205.1, C208.1, D702.1 (A), U201.4 (PVDD), U201.20 (VSYS), U201.32 (VOUT2), U202.5 (VIN); also elsewhere on the board

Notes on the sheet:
Strapping and connections (from the datasheet): - VBUS from dock pad VIN. VBUS abs max 22 V; OVP 5.5 V typ; VBUSPOR 3.9 V. The VIN TVS (D601) is on the dock sheet, at the pad. - CC1/CC2 to GND: no USB-C; VBUS limit stays at the 100 mA default (enough for the 30 mA charge current). - VBUSOUT not use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
(check) before freezing: - U201 footprint: KiCad QFN-32 5x5 EP 3.45 mm; datasheet EP is 3.5 nom (3.4-3.6). Compare with Nordic's QFN reference layout. - U201 has no LCSC stock (only the nPM1304-EK, C50090302); source the chip elsewhere or as a consigned part. - L201: Murata DFE201610E-2R2M confirme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
nPM1304 power sheet (step 3). Based on Nordic nPM1304 datasheet, reference circuit 'Configuration 2' (QFN): one buck, no LDO/load switch, ship-mode exit and NTC used. Draft until the Stage 0b nPM1304-EK tests.

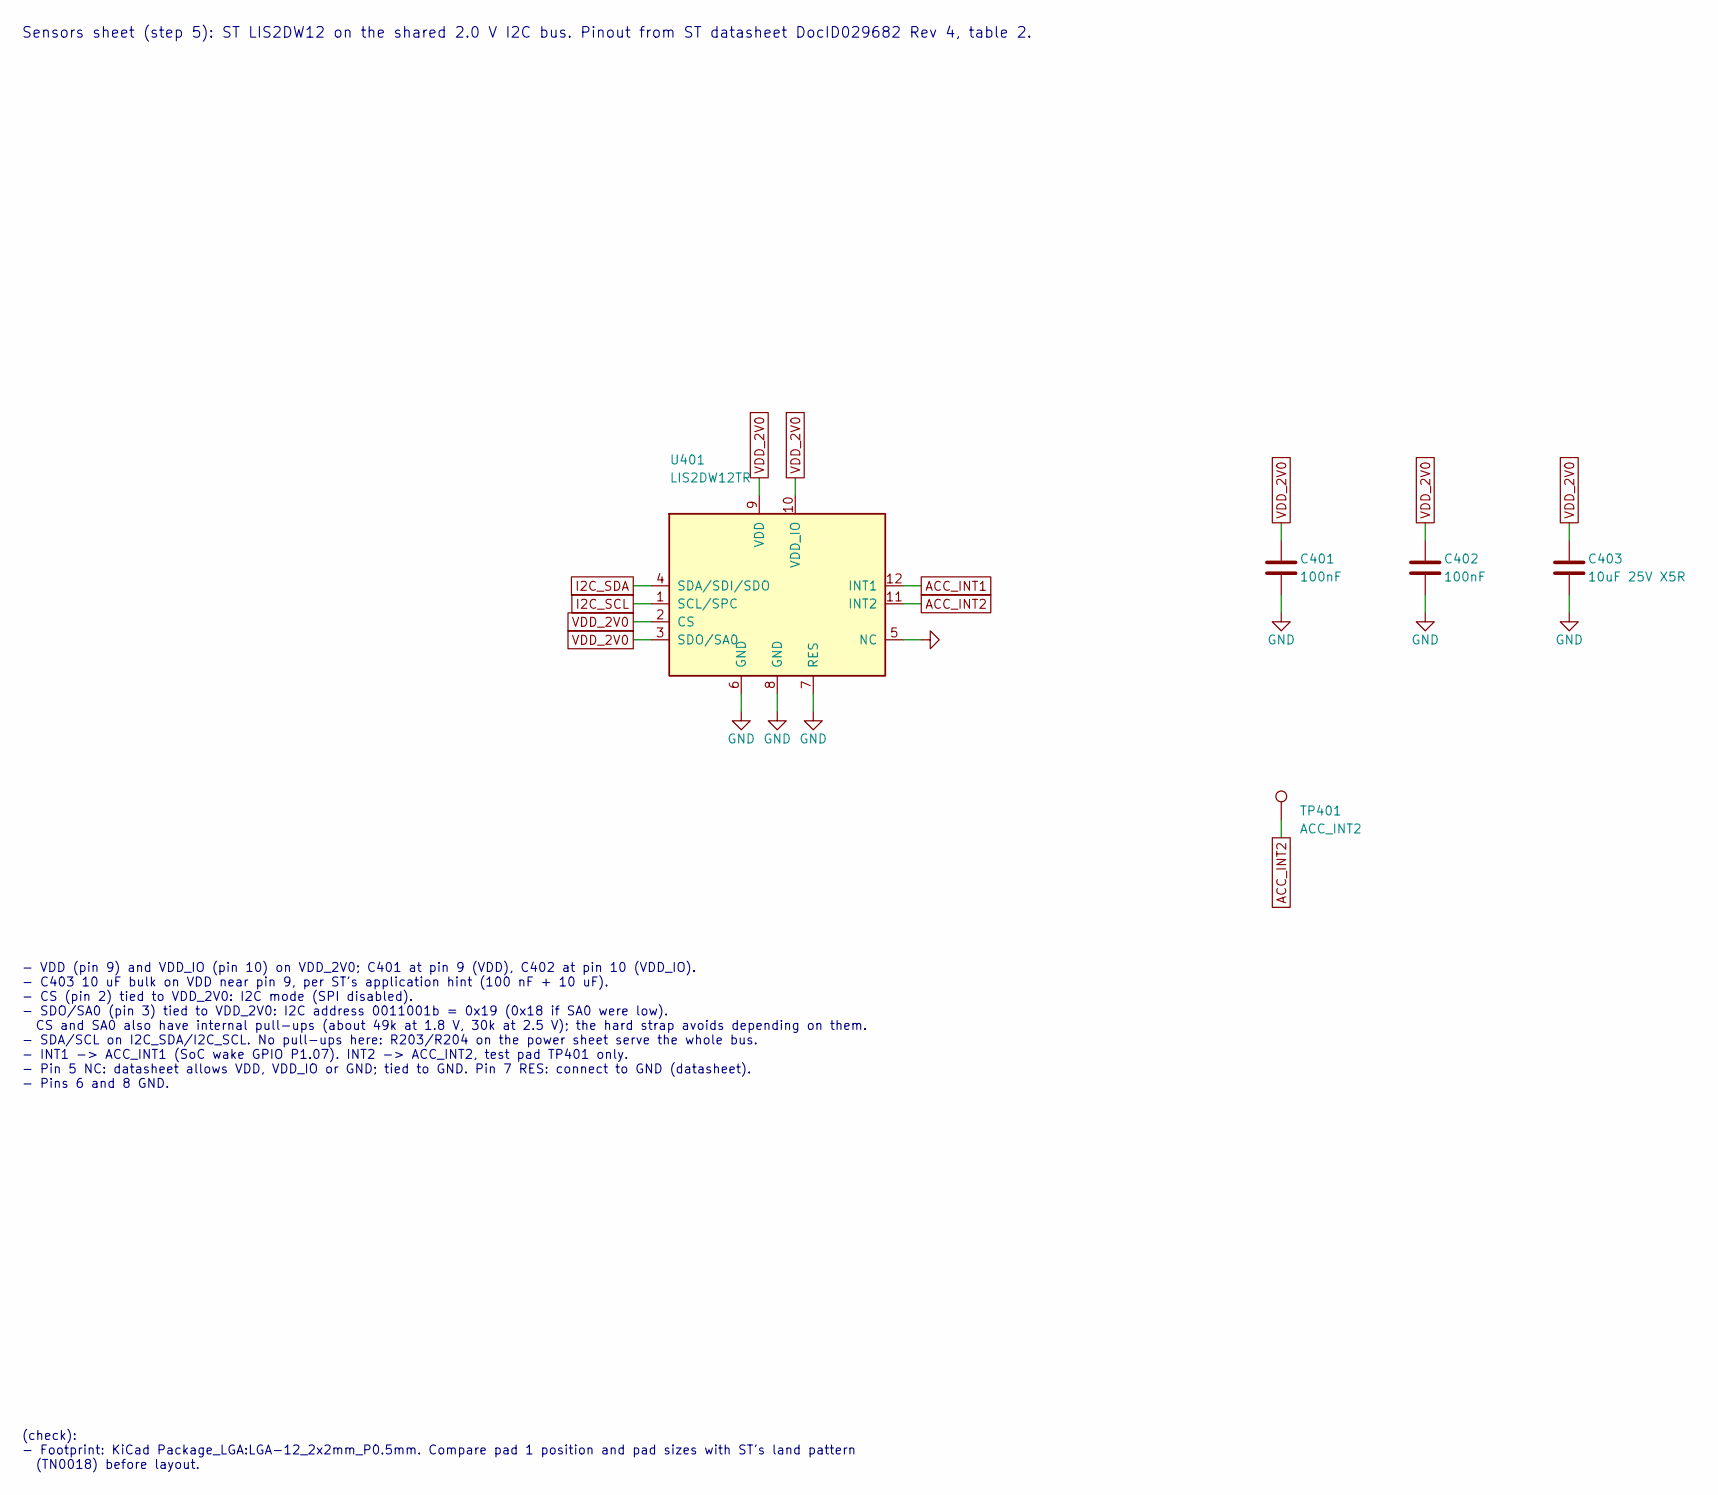
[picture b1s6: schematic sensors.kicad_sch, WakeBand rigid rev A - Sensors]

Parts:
C401, C402: 100nF; C_0402_1005Metric; LCSC C1525
C403: 10uF 25V X5R; C_0603_1608Metric; LCSC C96446
TP401: ACC_INT2; TestPoint_Pad_D0.8mm
U401: LIS2DW12TR; LGA-12_2x2mm_P0.5mm; LCSC C189624

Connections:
ACC_INT1: U401.12 (INT1); also elsewhere on the board
ACC_INT2: TP401.1, U401.11 (INT2)
GND: C401.2, C402.2, C403.2, U401.5 (NC), U401.6 (GND), U401.7 (RES), U401.8 (GND); also elsewhere on the board
I2C_SCL: U401.1 (SCL/SPC); also elsewhere on the board
I2C_SDA: U401.4 (SDA/SDI/SDO); also elsewhere on the board
VDD_2V0: C401.1, C402.1, C403.1, U401.2 (CS), U401.3 (SDO/SA0), U401.9 (VDD), U401.10 (VDD_IO); also elsewhere on the board

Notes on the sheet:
(check): - Footprint: KiCad Package_LGA:LGA-12_2x2mm_P0.5mm. Compare pad 1 position and pad sizes with ST's land pattern (TN0018) before layout.
Sensors sheet (step 5): ST LIS2DW12 on the shared 2.0 V I2C bus. Pinout from ST datasheet DocID029682 Rev 4, table 2.
- VDD (pin 9) and VDD_IO (pin 10) on VDD_2V0; C401 at pin 9 (VDD), C402 at pin 10 (VDD_IO). - C403 10 uF bulk on VDD near pin 9, per ST's application hint (100 nF + 10 uF). - CS (pin 2) tied to VDD_2V0: I2C mode (SPI disabled). - SDO/SA0 (pin 3) tied to VDD_2V0: I2C address 0011001b = 0x19 (0x18 if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
